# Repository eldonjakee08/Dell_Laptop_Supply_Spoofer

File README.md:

# Dell Laptop Supply Spoofer
yowyow

So I have this old Dell Inspiron 3593 (2020 model) laptop and it's showing its age, with the battery being slightly bloated and high wear level of 40%. 😅

I know! I know! I should replace the battery 😅, but I kind of thought "hey why not power the laptop with an external powerbank?" in that way I'm not limited to the laptops internal battery. I could use my laptop anywhere for many hours without having to worry about a power source. 

I'm an outdoor person and sometimes I get claustrophobic inside coding all day, I would like to sometimes code outdoors, like by the beach, by the park or even in cafes. But with the current state of my laptops battery, I am not able to do those things and that's the main motivation behind this little project. 

# Defining the problem
So due to my laptops relatively old age (5 years is considered old in tech years 😂), it comes installed with a 4.5mm DC power jack. So challenge #1 is, how do I convert the Type-C port that comes with modern power banks into a 4.5mm DC power jack? My answer to that is with these little guys, USB PD trigger boards.  

These boards are designed to trigger a USB Power Delivery (USB PD) capable power bank to output a specific voltage level (i.e 5V, 9V, 12V, 15V & 20V) we can then solder on its output pins a 4.5mm DC Jack cable which we can plug into the laptop. As for the power source, we will be using a 65Watt USB PD capable power bank that can output 20V and source up to 3.25A. 

So by using a 65W USB PD capable power bank + USB PD Trigger module + 4.5mm DC Power jack cable and plugging it into the laptop would make this work right???

Well, not quite, because Dell laptop power supplies implement an ID chip on its output stage for authenticity checking, output voltage check & output power check. 

If you just plug in a random 20V supply into the laptop it would know that it's not an authentic dell laptop supply and it would severely limit the amount of current that it would draw from it (800mA in my experience) which results in an underpowered & underclocked laptop leading to poor performance. This is our challenge #2, how to bypass the dell proprietary handshake between supply and laptop. 

Notice from the schematic, Dell uses a DS2501 EEPROM IC for its ID chip, which is a 512bit 1-Wire protocol EEPROM chip. This is where the serial number and power supply details are stored, which is then read by the laptop when the power supply is first plugged in. So in theory, if we read the data inside the DS2501 EEPROM, program it into our own ID chip and wire the data pin into the ID pin of our 4.5mm DC power jack, we should be able to bypass the authenticity check. 

So now, the whole system should look like this: 

# Probing the ID Chip
So I probed the ID pin of the supply with a logic analyzer to see the data being exchanged during handshake. Heres what I got. 

<br>

RESET CONDITION: The laptop issues a ~500us pulse to check if a 1-Wire slave (DS2501) is present.

PRESENCE PULSE: The DS2501 responds with a presence pulse to let the laptop know its "presence"      
<br>

SKIP ROM COMMAND: This is a 1-Wire protocol command that basically tells the DS2501 IC to skip the slave identification process.

READ MEMORY COMMAND: This command (0xF0) is used to read data inside the DS2501 EEPROM data field. 

<br>

The bus master (the laptop) follows the read memory command byte with a 2-byte address TA1:(T7:T0) = 0x06 (lower nibble address), TA2:(T15:T8) = 0x00 (higher nibble address) that indicates a starting address location within the EEPROM data field.

<br>**DATA SECTION**

DATA 0x27: This is an 8-bit CRC of the command byte and address bytes which is computed by the DS2501.

DATA 0x41,'A': Data inside memory address 0x0006 which is the start address of the READ ROM command. DS2501 auto increments the address if the master issues more read time slots. 

DATA 0x43,'C': Data inside memory address 0x0007.

DATA 0x30,'0': Data inside memory address 0x0008.

DATA 0x36,'6': Data inside memory address 0x0009.

DATA 0x35,'5': Data inside memory address 0x000A.

So if you notice, the data reads "AC065" this basically tells the laptop that its an "AC" supply thats capable of outputting 65Watts! So if we just program these values on the same memory location in our own ID chip then we could essentially bypass the handshake. 

I tried reading the whole EEPROM of the ID chip and this is what i got. 

DELL00AC065195033CN0MGJN9LOC0001V8314A08

DELL: Power supply manufacturer

AC: AC supply

65: 65 Watts capable

195: 19.5 Output Voltage

33CN0MGJN9LOC0001V8314A08: Laptop Supply Serial Number

Now we have the values to program into our ID chip! 

# Programming the ID Chip

The dell laptop supplies use a DS2501 ID Chip, I have a few problems on using this chip:

1. Its a one time programmable chip.
2. You need a 12V pulse applied to the data pins to program the EEPROM. Which we would need a separate circuit for precise 12V pulse generation.
3. Lastly, IT'S OBSOLETE! 😭

So instead, I opted for a newer chip in the same family, the DS2431 1024bit 1-Wire EEPROM IC. I think this is an improvement over the now obsolete DS2501 for the following reasons:

1. You could program the EEPROM multiple times.
2. You do not need a 12V pulse to program the chip.
3. Same EEPROM addresses and memory structure as DS2501.
4. Same ROM commands as DS2501
5. Larger memory.
6. Lastly, ITS NOT OBSOLETE! 👌

I've developed a driver for programming and reading into the EEPROM of these chips. You can download and refer to the Repo link given below on how to use the driver.

Repo Link: https://github.com/eldonjakee08/DS2431_1WIRE_EEPROM_DRIVER

I made a simple STM32 program to write into the EEPROM. Let me explain how it works. 
1. declare and intialize uint8_t pdata[] array, this will hold the first 8 bytes of data to be written into EEPROM memory location 0x0000 to 0x0007
2. call OneWire_WriteMemory() function (from the driver) to write the contents of pdata array into DS2431s EEPROM
3. declare and intialize another uint8_t pdata2[] array, this will hold the 2nd batch of 8 byte data to be written into memory location 0x0008 to 0x000F
4. call OneWire_WriteMemory() function again to write the contents of pdata2 array into DS2431s EEPROM

If you notice, in pdata[] array, theres this "0x27" byte. This data is actually the 8bit CRC generated by the DS2501 after master issues the SKIP ROM, READ MEMORY & MEMORY LOCATION commands. 

The problem with DS2431 is that, it does not generate an 8Bit CRC after master issues the previously mentioned commands. The laptop expects to get the 0x27 CRC from slave, so to solve this, we hard coded the 0x27 8bit CRC into the memory location 0x0006 of DS2431 EEPROM. 

This particular memory location is important as this is where the laptop starts to read from the ID chips EEPROM. So by the time the laptop expects an 8Bit CRC from the slave, what the DS2431 essentially does is sending the hard coded 0x27 CRC data inside the memory location 0x0006, thereby replicating the DS2501 behavior. 👌

After programming the chip we should get a message in the Serial Wire Viewer. (Shown below)

Now that we have programmed the chip, we can now proceed in assembling the hardware. 

# Assembling the Hardware

The hardware for this project is pretty simple. See schematic below. 

The output of the PD trigger is directly connected to the power lines of the 4.5mm DC jack cable. The data line of the DS2431 is directly connected to the ID line of the cable. 

If you notice, the DS2431 does not have any power rails, this is because the IC can operate in "parasitic power mode" this essentially means that it draws its power from the data lines during the read/write process. 

<br>**END PRODUCT**

<br>**TESTING**

Heres a youtube video of me testing the Supply Spoofer.

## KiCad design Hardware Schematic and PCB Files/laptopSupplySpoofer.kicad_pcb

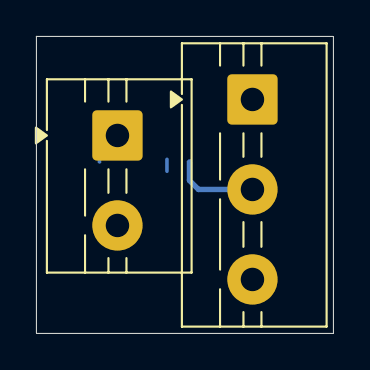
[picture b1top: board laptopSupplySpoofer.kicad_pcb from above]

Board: 2 copper layers, 16.5 x 16.5 mm, 3 parts (1 on the bottom side), 3 nets.

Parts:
J1: Screw_Terminal_01x02; TerminalBlock_MaiXu_MX126-5.0-02P_1x02_P5.00mm
J2: Screw_Terminal_01x03; TerminalBlock_MaiXu_MX126-5.0-03P_1x03_P5.00mm
U1: DS2431P; TSOC-6_3.76x3.94mm_P1.27mm

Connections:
1WIRE: J2.2, U1.2 (IO)
+20V: J1.2, J2.3
GND: J1.1, J2.1, U1.1 (GND)

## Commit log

2025-09-19 added project files
2025-10-24 changed readme
2025-10-24 modify readme main branch
2025-10-24 readme file modify
2025-10-24 modify to original readme
2025-10-24 feature branch added
